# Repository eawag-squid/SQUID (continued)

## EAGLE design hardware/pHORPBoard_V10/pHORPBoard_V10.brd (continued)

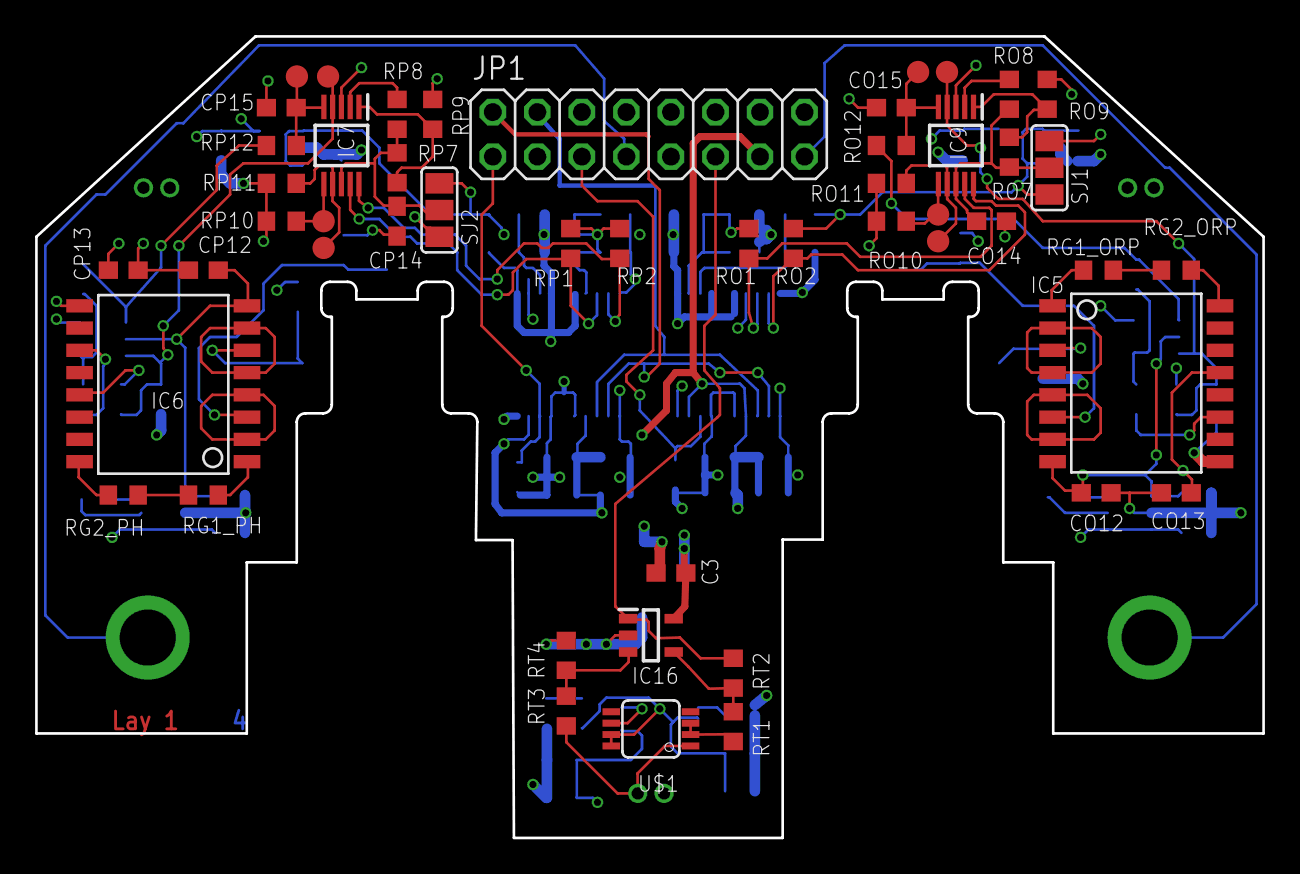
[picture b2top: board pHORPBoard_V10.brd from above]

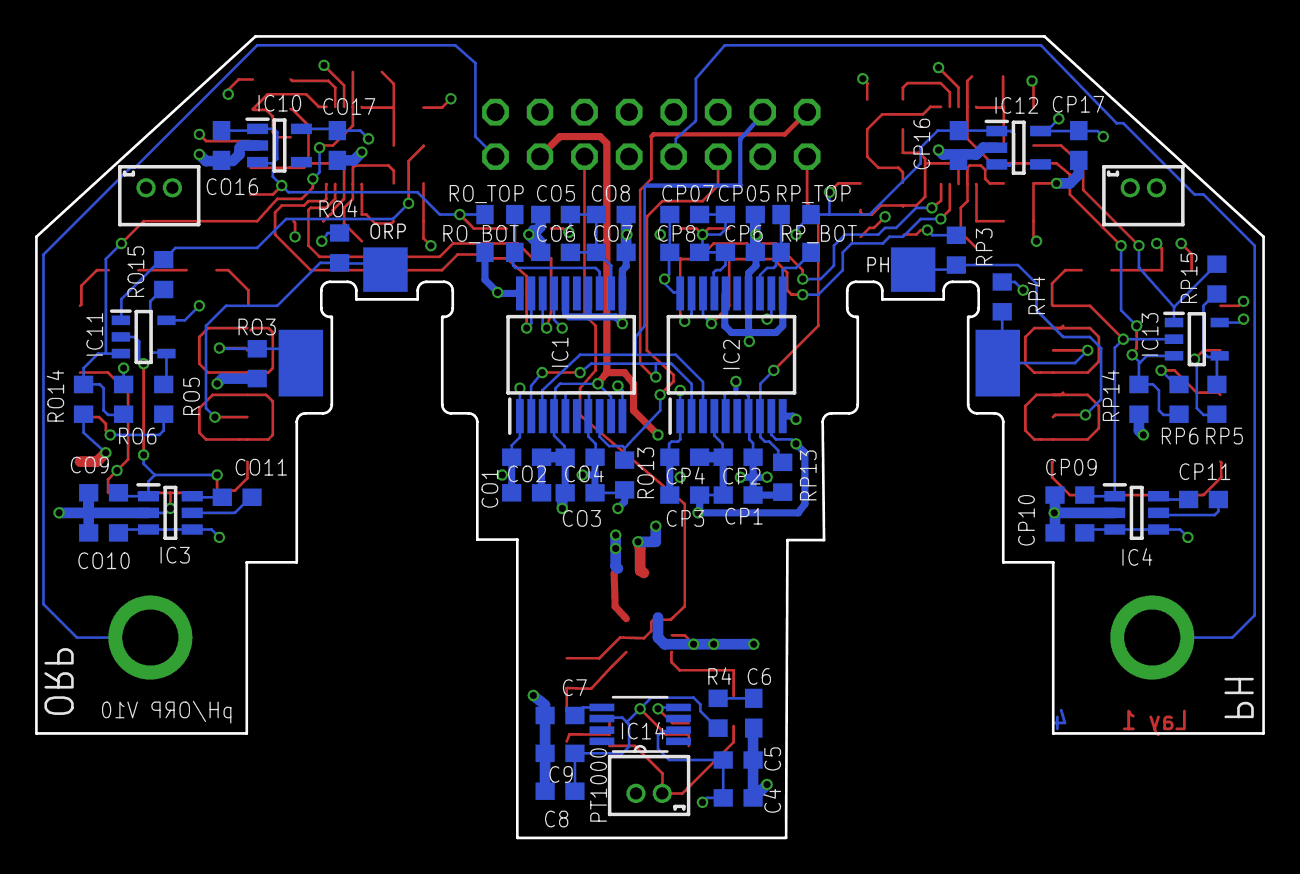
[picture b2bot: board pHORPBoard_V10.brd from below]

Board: 4 copper layers, 70.0 x 45.7 mm, 115 parts (65 on the bottom side), 67 nets.

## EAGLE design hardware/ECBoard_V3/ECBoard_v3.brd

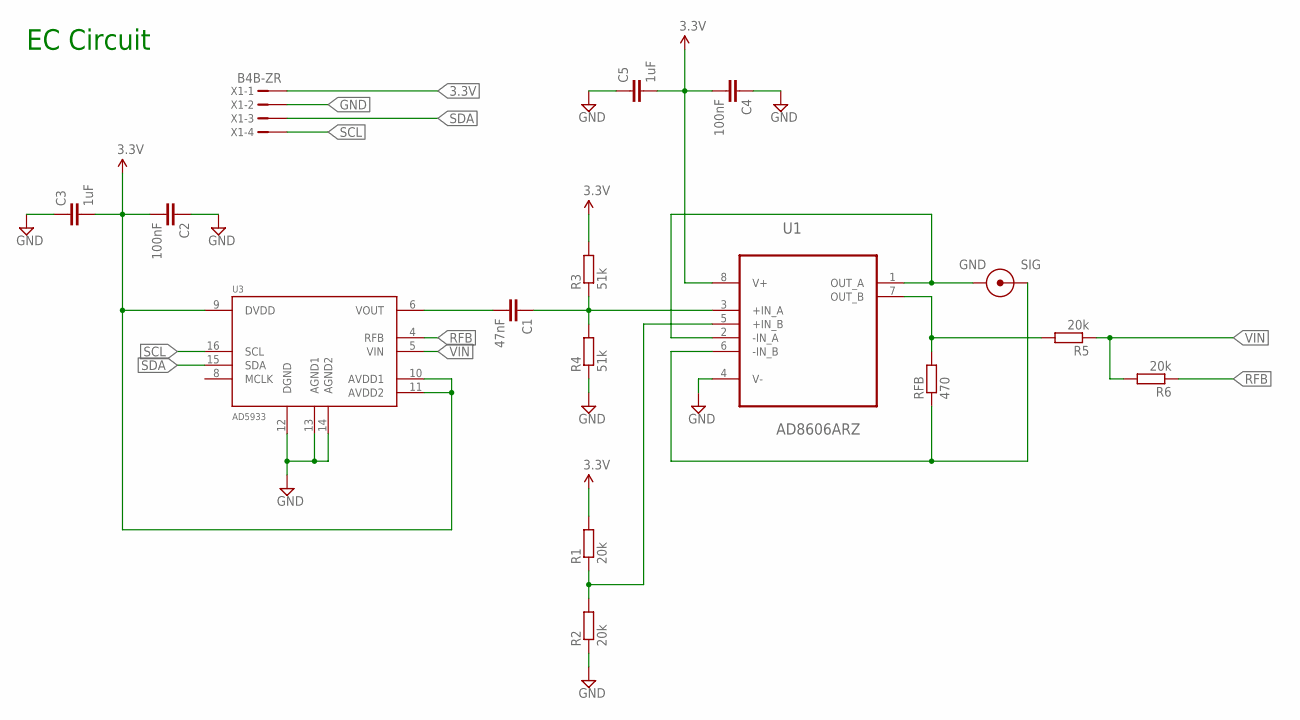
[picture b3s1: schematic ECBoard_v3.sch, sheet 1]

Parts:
C1: 47nF; C0805
C2, C4: 100nF; C0805
C3, C5: 1uF; C0805
R1, R2, R5, R6: 20k; R0805
R3, R4: 51k; R0805
RFB: 470; R0805
U1: AD8606ARZ; SOIC127P600X175-8N
U3: AD5933; SSOP16
U$1: CON_HANNA
X1: B4B-ZR

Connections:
3.3V: C2.2, C3.2, C4.2, C5.2, R1.2, R3.2, U1.8 (V+), U3.9 (DVDD), U3.10 (AVDD1), U3.11 (AVDD2), X1.1; also elsewhere on the board
GND: C2.1, C3.1, C4.1, C5.1, R2.1, R4.1, U1.4 (V-), U3.12 (DGND), U3.13 (AGND1), U3.14 (AGND2), X1.2; also elsewhere on the board
unnamed: C1.1, R3.1, R4.2, U1.3 (+IN_A)
unnamed: U1.1 (OUT_A), U1.2 (-IN_A), U$1.CON_GND
unnamed: C1.2, U3.6 (VOUT)
unnamed: RFB.1, U1.6 (-IN_B), U$1.CON_SIG
unnamed: R1.1, R2.2, U1.5 (+IN_B)
unnamed: R5.2, RFB.2, U1.7 (OUT_B)
RFB: R6.1, U3.4 (RFB)
SCL: U3.16 (SCL), X1.4
SDA: U3.15 (SDA), X1.3
VIN: R5.1, R6.2, U3.5 (VIN)

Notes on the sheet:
EC Circuit

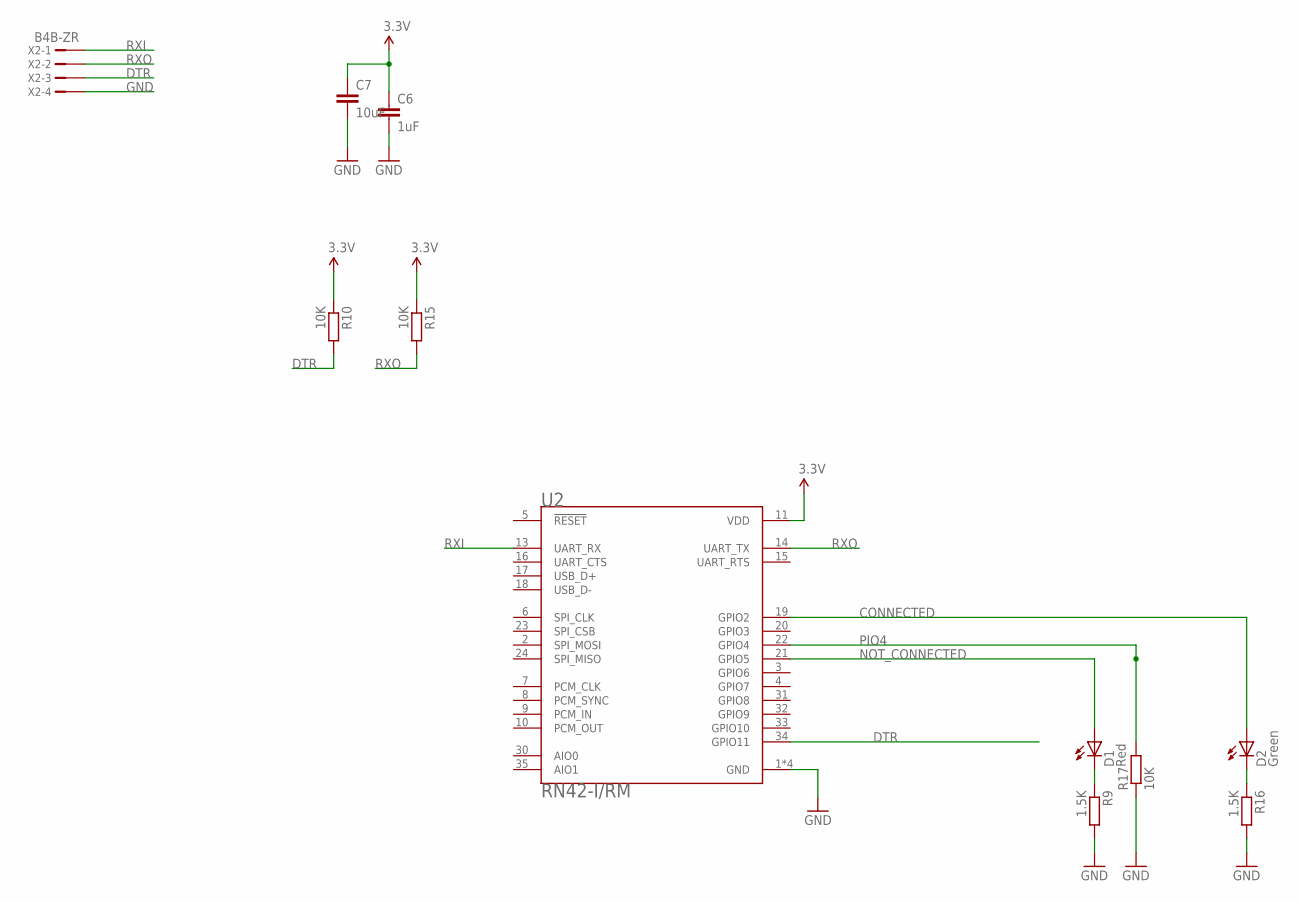
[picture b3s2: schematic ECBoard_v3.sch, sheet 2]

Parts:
C6: 1uF; C0805
C7: 10uF; C0805
D1: Red; LED-0603
D2: Green; LED-0603
R9, R16: 1.5K; R0805
R10, R15, R17: 10K; R0805
U2: RN42-I/RM; XCVR_RN42-I/RM
X2: B4B-ZR

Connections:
3.3V: C6.1, C7.1, R10.1, R15.1, U2.11 (VDD); also elsewhere on the board
CONNECTED: D2.A, U2.19 (GPIO2)
D1: D1.C, R9.1
D2: D2.C, R16.1
DTR: R10.2, U2.34 (GPIO11), X2.3
GND: C6.2, C7.2, R9.2, R16.2, R17.1, U2.1 (GND), U2.12 (GND), U2.28 (GND), U2.29 (GND), X2.4; also elsewhere on the board
NOT_CONNECTED: D1.A, U2.21 (GPIO5)
PIO4: R17.2, U2.22 (GPIO4)
RXI: U2.13 (UART_RX), X2.1
RXO: R15.2, U2.14 (UART_TX), X2.2

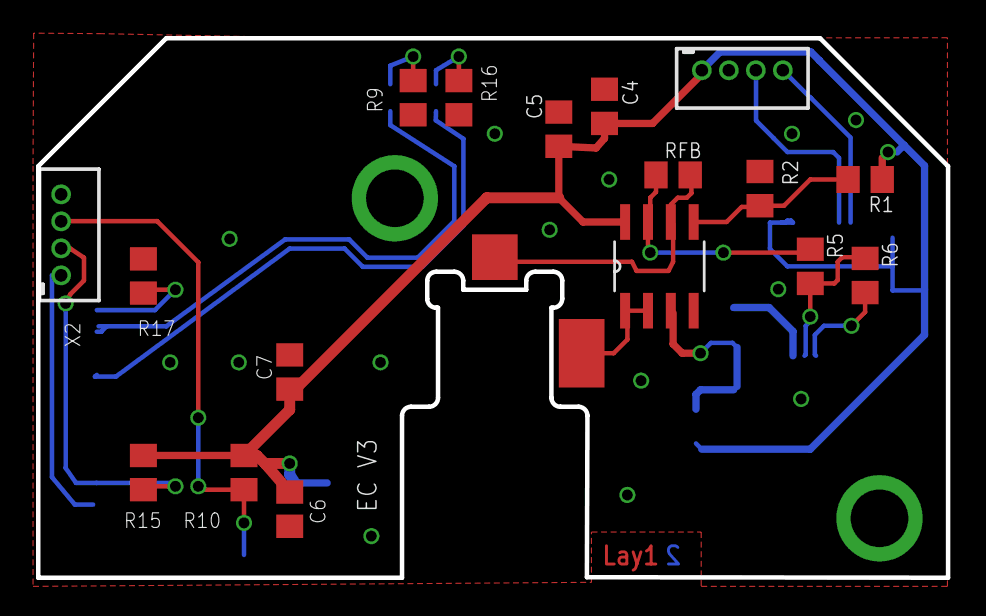
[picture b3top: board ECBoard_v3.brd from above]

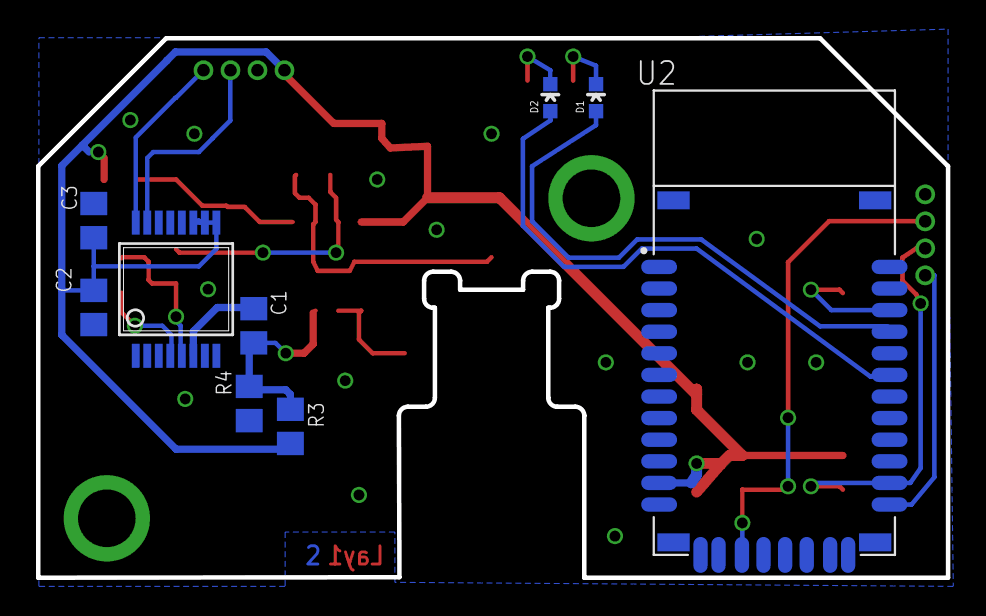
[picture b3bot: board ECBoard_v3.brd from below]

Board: 2 copper layers, 50.5 x 30.0 mm, 27 parts (9 on the bottom side), 20 nets.

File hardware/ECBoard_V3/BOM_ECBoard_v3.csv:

ECBoard_V3;;;;
;;;;
;;;;
;;;;
Reference designators;Quantity;MPN;Manufacturer;Description
R9, R16;2;GPR08051K5;Generic part;0805, Res 1.5kOhm, 150V, 1.0%, 125mW
C2, C4;2;GPC0805104;Generic part;0805, Cap 100.0nF, 50V, 10.0%, X7R
R10, R15, R17;3;GPR080510K;Generic part;0805, Res 10.0kOhm, 150V, 1.0%, 125mW
C7;1;GPC0805106-16;Generic part;0805 MLCC X5R 10UF 10% 16V
C3, C5, C6;3;GPC0805105;Generic part;0805, Cap 1uF, 50V, 10.0%, X7R
R1, R2, R5, R6;4;GPR080520K;Generic part;0805, Res 20.0kOhm, 150V, 1.0%, 125mW
RFB;1;GPR0805470R;Generic part;0805, Res 470.0Ohm, 150V, 1.0%, 125mW
C1;1;GPC0805473;Generic part;0805, Cap 47.0nF, 50V, 10.0%, X7R
R3, R4;2;GPR080551K;Generic part;0805, Res 51.0kOhm, 150V, 1.0%, 125mW
U3;1;AD5933YRSZ;Analog Device;Data Acquisition ADCs/DACs - Specialised IC 12bit 1 MSPS Impedance Cnvtr
U1;1;AD8606ARZ;Analog Devices;General Purpose Amplifier 2 Circuit Rail-to-Rail 8-SOIC
X1, X2;2;B4B-ZR(LF)(SN);JST;"4 Positions Header Connector 0.059"" (1.50mm) Through Hole Tin"
U4;1;RN42-I/RM;Microchip Technology;RF TXRX MOD BLUETOOTH TRACE ANT
D2;1;LT Q39E-Q1OO-25-1;OSRAM Opto Semiconductors Inc.;Green 530nm LED Indication - Discrete 2.85V 0603 (1608 Metric)
D1;1;LS Q976-NR-1;Osram Opto;Red 633nm LED Indication - Discrete 2V 0603 (1608 Metric)

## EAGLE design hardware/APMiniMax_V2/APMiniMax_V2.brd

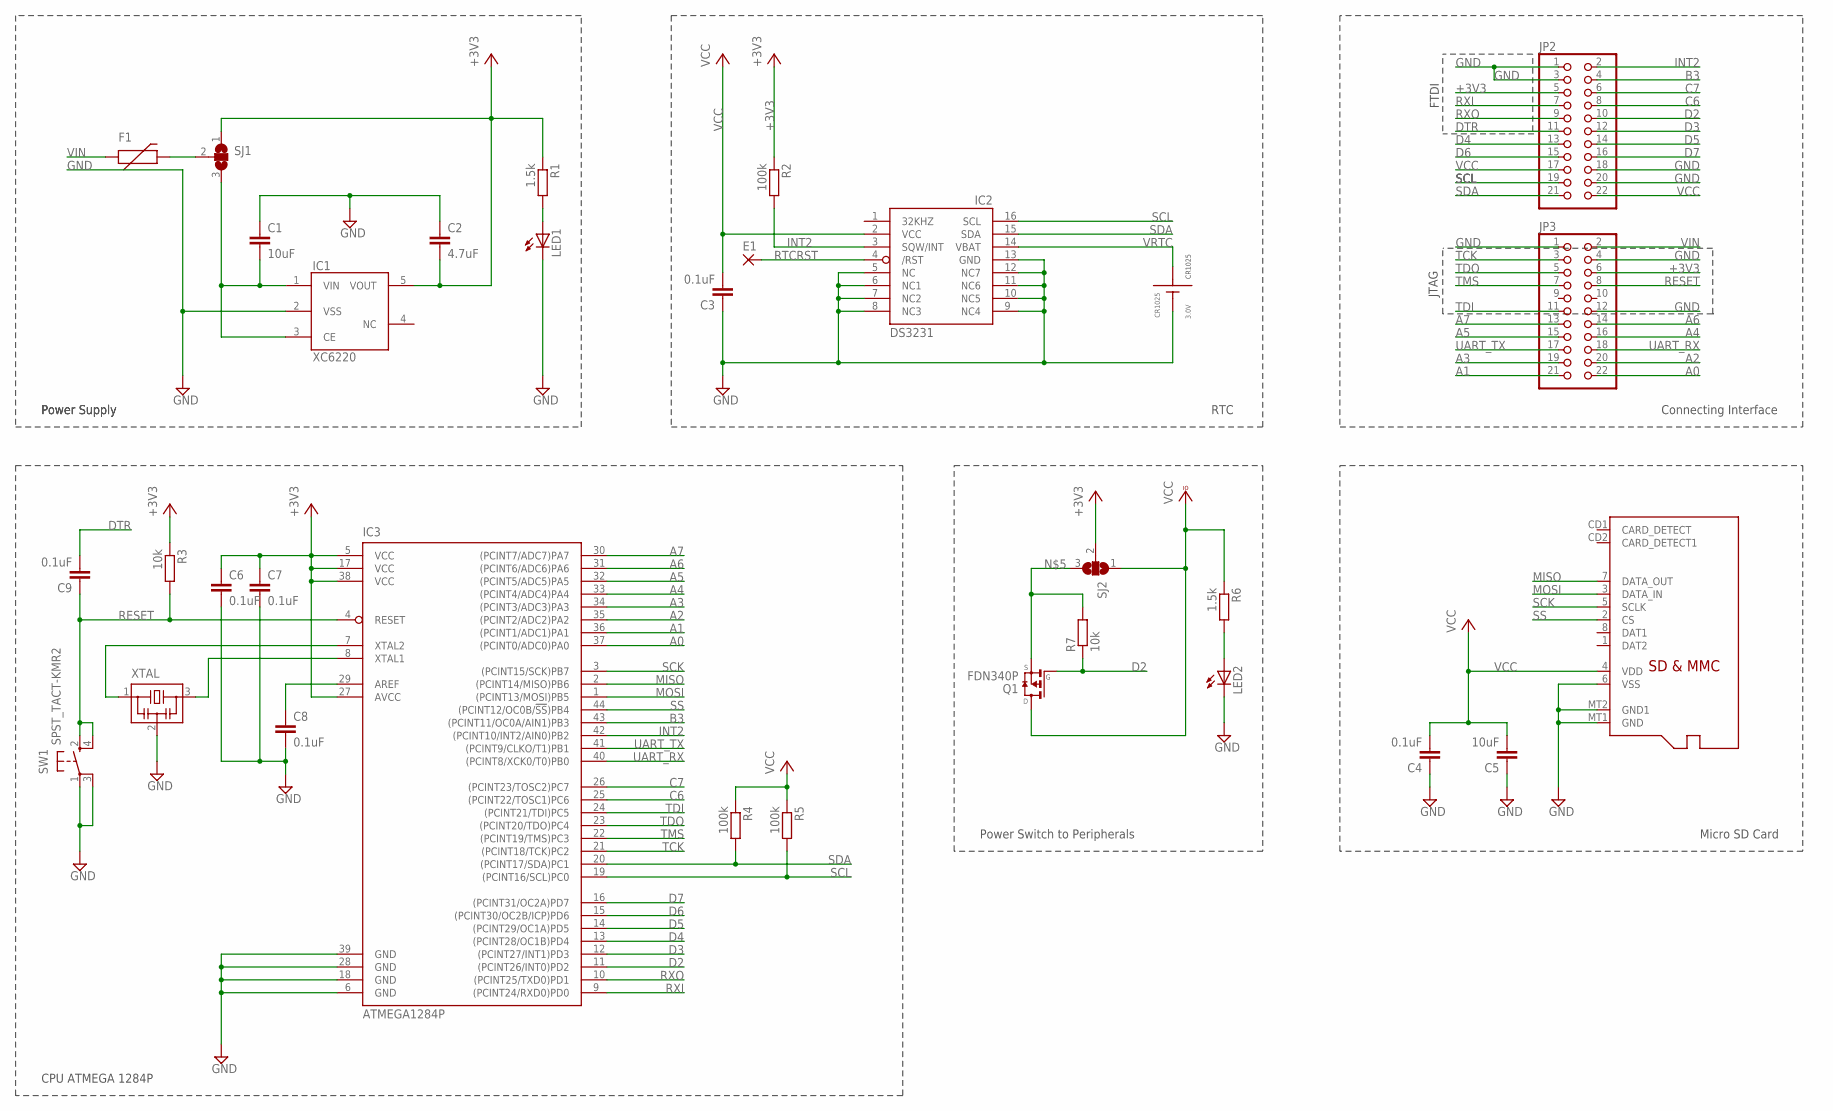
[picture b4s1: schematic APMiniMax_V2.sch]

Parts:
C1, C5: 10uF; C1206
C2: 4.7uF; C1206
C3, C4, C6, C7, C8, C9: 0.1uF; C0805
CR1025: 3.0V; CR1025SMD
E1: 0,75/0,5
F1: FUSE0805; R0805
IC1: XC6220SOT-25; SOT25
IC2: DS3231/SO; SO16W
IC3: ATMEGA1284P; TQFP44
JP2, JP3: PINHD-2X11; 2X11
LED1, LED2: LEDCHIP-LED0805; CHIP-LED0805
MMC: MICROSD
Q1: FDN340P; SSOT-3
R1, R6: 1.5k; R0805
R2, R4, R5: 100k; R0805
R3, R7: 10k; R0805
SJ1, SJ2: SJ2W; SJ_2
SW1: SPST_TACT-KMR2; KMR2
XTAL: CSTCE8M00G52-R0; CSTCE

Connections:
+3V3: C2.2, C6.1, C7.1, IC1.5 (VOUT), IC3.5 (VCC), IC3.17 (VCC), IC3.27 (AVCC), IC3.38 (VCC), JP2.5, JP3.6, R1.1, R2.1, R3.1, SJ1.1, SJ2.2
A0: IC3.37 ((PCINT0/ADC0)PA0), JP3.22
A1: IC3.36 ((PCINT1/ADC1)PA1), JP3.21
A2: IC3.35 ((PCINT2/ADC2)PA2), JP3.20
A3: IC3.34 ((PCINT3/ADC3)PA3), JP3.19
A4: IC3.33 ((PCINT4/ADC4)PA4), JP3.16
A5: IC3.32 ((PCINT5/ADC5)PA5), JP3.15
A6: IC3.31 ((PCINT6/ADC6)PA6), JP3.14
A7: IC3.30 ((PCINT7/ADC7)PA7), JP3.13
AREF: C8.1, IC3.29 (AREF)
B3: IC3.43 ((PCINT11/OC0A/AIN1)PB3), JP2.4
C6: IC3.25 ((PCINT22/TOSC1)PC6), JP2.8
C7: IC3.26 ((PCINT23/TOSC2)PC7), JP2.6
D2: IC3.11 ((PCINT26/INT0)PD2), JP2.10, Q1.1 (G), R7.1
D3: IC3.12 ((PCINT27/INT1)PD3), JP2.12
D4: IC3.13 ((PCINT28/OC1B)PD4), JP2.13
D5: IC3.14 ((PCINT29/OC1A)PD5), JP2.14
D6: IC3.15 ((PCINT30/OC2B/ICP)PD6), JP2.15
D7: IC3.16 ((PCINT31/OC2A)PD7), JP2.16
DTR: C9.2, JP2.11
GND: C1.1, C2.1, C3.1, C4.1, C5.1, C6.2, C7.2, C8.2, CR1025.GND, IC1.2 (VSS), IC2.5 (NC), IC2.6 (NC1), IC2.7 (NC2), IC2.8 (NC3), IC2.9 (NC4), IC2.10 (NC5), IC2.11 (NC6), IC2.12 (NC7), IC2.13 (GND), IC3.6 (GND), IC3.18 (GND), IC3.28 (GND), IC3.39 (GND), JP2.1, JP2.3, JP2.18, JP2.20, JP3.1, JP3.4, JP3.12, LED1.C, LED2.C, MMC.6 (VSS), MMC.MT1 (GND), MMC.MT2 (GND1), SW1.1, SW1.3 (P1), XTAL.2
INT2: IC2.3 (SQW/INT), IC3.42 ((PCINT10/INT2/AIN0)PB2), JP2.2, R2.2
MISO: IC3.2 ((PCINT14/MISO)PB6), MMC.7 (DATA_OUT)
MOSI: IC3.1 ((PCINT13/MOSI)PB5), MMC.3 (DATA_IN)
unnamed: LED1.A, R1.2
unnamed: F1.2, SJ1.2
unnamed: C1.2, IC1.1 (VIN), IC1.3 (CE), SJ1.3
unnamed: Q1.2 (S), R7.2, SJ2.3
unnamed: IC3.7 (XTAL2), XTAL.1
unnamed: IC3.8 (XTAL1), XTAL.3
unnamed: LED2.A, R6.2
RESET: C9.1, IC3.4 (RESET), JP3.8, R3.2, SW1.2 (S), SW1.4 (S1)
RTCRST: E1.1, IC2.4 (/RST)
RXI: IC3.9 ((PCINT24/RXD0)PD0), JP2.7
RXO: IC3.10 ((PCINT25/TXD0)PD1), JP2.9
SCK: IC3.3 ((PCINT15/SCK)PB7), MMC.5 (SCLK)
SCL: IC2.16 (SCL), IC3.19 ((PCINT16/SCL)PC0), JP2.19, R5.2
SDA: IC2.15 (SDA), IC3.20 ((PCINT17/SDA)PC1), JP2.21, R4.2
SS: IC3.44 ((PCINT12/OC0B/!SS!)PB4), MMC.2 (CS)
TCK: IC3.21 ((PCINT18/TCK)PC2), JP3.3
TDI: IC3.24 ((PCINT21/TDI)PC5), JP3.11
TDO: IC3.23 ((PCINT20/TDO)PC4), JP3.5
TMS: IC3.22 ((PCINT19/TMS)PC3), JP3.7
UART_RX: IC3.40 ((PCINT8/XCK0/T0)PB0), JP3.18
UART_TX: IC3.41 ((PCINT9/CLKO/T1)PB1), JP3.17
VCC: C3.2, C4.2, C5.2, IC2.2 (VCC), JP2.17, JP2.22, MMC.4 (VDD), Q1.3 (D), R4.1, R5.1, R6.1, SJ2.1
VIN: F1.1, JP3.2
VRTC: CR1025.V+@1 (V+), CR1025.V+@2 (V+), IC2.14 (VBAT)

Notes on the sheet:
JTAG
FTDI
Power Supply
CPU ATMEGA 1284P
RTC
Connecting Interface
Micro SD Card
Power Switch to Peripherals

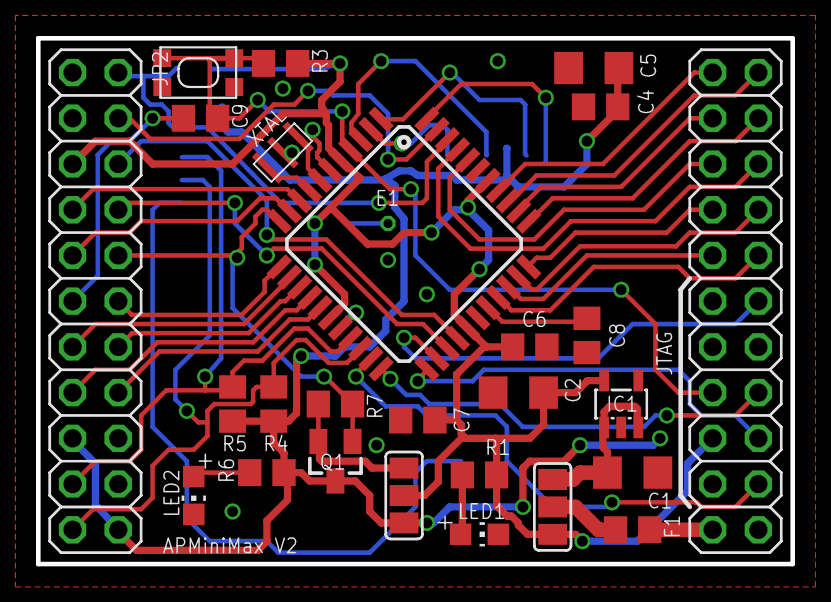
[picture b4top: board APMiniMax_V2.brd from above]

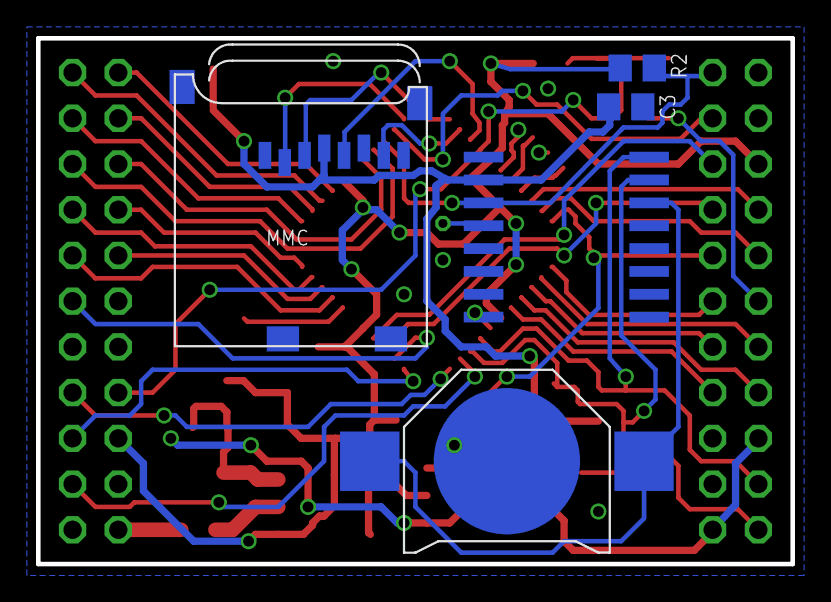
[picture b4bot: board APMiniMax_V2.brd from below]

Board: 2 copper layers, 41.9 x 29.2 mm, 32 parts (5 on the bottom side), 48 nets.

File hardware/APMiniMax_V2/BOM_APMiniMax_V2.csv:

APMiniMax;;;;
;;;;
Reference designators;Quantity;MPN;Manufacturer;Description
C1, C5;2;GPC1206106-B;Generic part;"10µF 25V Ceramic Capacitor X5R 1206 (3216 Metric) 0.126"" L x 0.063"" W (3.20mm x 1.60mm)"
C2;1;GPC1206475;Generic part;4.7µF ±10% 25V Ceramic Capacitor X7R 1206 (3216 Metric)
C3, C4, C6, C7, C8, C9;6;GPC0805104;Generic part;0805, Cap 100.0nF, 50V, 10.0%, X7R
F1;1;MF-PSMF035X-2;Bourns Inc.;Polymeric PTC Resettable Fuse 6V 350mA Ih Surface Mount 0805 (2012 Metric), Concave
IC1;1;XC6220B331MR-G;Torex Semiconductor;Linear Voltage Regulator IC Positive Fixed 1 Output 3.3V 1A SOT-25
IC2;1;DS3231SN#;Maxim Integrated;IC, Extremely Accurate I2C-Integrated RTC/TCXO/Crystal
IC3;1;ATMEGA1284P-AU;Atmel;ATmega Microcontroller IC 8-Bit 20MHz 128KB (64K x 16) FLASH 44-TQFP (10x10)
LED1, LED2;2;LTST-C171GKT;Lite-On;Green 569nm LED Indication - Discrete 2.1V 0805 (2012 Metric)
MMC;1;2908-05WB-MG;3M;10 (8 + 2) Position Card Connector Secure Digital - microSDâ¢ Surface Mount, Right Angle Gold
Q1;1;FDN340P;Fairchild Semiconductor;MOSFETP-Channel 20V 2A (Ta) 500mW (Ta) Surface Mount SuperSOT-3
R1, R6;2;GPR08051K5;Generic part;0805, Res 1.5kOhm, 150V, 1.0%, 125mW
R2, R4, R5;3;GPR0805100K;Generic part;0805, Res 100.0kOhm, 150V, 1.0%, 125mW
R3, R7;2;GPR080510K;Generic part;0805, Res 10.0kOhm, 150V, 1.0%, 125mW
SW1;1;KMR231NG LFS;C&K;Tactile Switch SPST-NO Top Actuated Surface Mount
XTAL;1;CSTCE8M00G52Z-R0;Murata;8MHz Ceramic Resonator Built in Capacitor 10pF ±0.1% -40°C ~ 125°C Surface Mount
CR1025;1;BK-870;MPD;Battery Retainer Coin, 10.0mm 1 Cell SMD (SMT) Tab

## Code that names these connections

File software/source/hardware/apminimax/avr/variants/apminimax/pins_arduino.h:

#ifndef Pins_Arduino_h
#define Pins_Arduino_h

#include <avr/pgmspace.h>

//                    ATMEL ATMEGA1284P 
//                    Pinout with VQFN case, just for visualization
//
//                               +---\/---+
//            PCINT8 (D14) PB0  1|        |40  PA0 (AI 0 / D24) PCINT0
//            PCINT9 (D15) PB1  2|        |39  PA1 (AI 1 / D25) PCINT1
//      PCINT10/INT2 (D 8) PB2  3|        |38  PA2 (AI 2 / D26) PCINT2
//      PCINT11/OC0A*(D 9) PB3  4|        |37  PA3 (AI 3 / D27) PCINT3
//   PCINT12/0C0B/SS*(D10) PB4  5|        |36  PA4 (AI 4 / D28) PCINT4
//      PCINT13/MOSI (D11) PB5  6|        |35  PA5 (AI 5 / D29) PCINT5
// PCINT14/OC3A/MISO*(D12) PB6  7|        |34  PA6 (AI 6 / D30) PCINT6
//  PCINT15/OC3B/SCK*(D13) PB7  8|        |33  PA7 (AI 7 / D31) PCINT7
//                         RST  9|        |32  AREF
//                         VCC 10|        |31  GND
//                         GND 11|        |30  AVCC
//                       XTAL2 12|        |29  PC7 (D23) TOSC2/PCINT23
//                       XTAL1 13|        |28  PC6 (D22) TOSC1/PCINT22
//       PCINT24/RX0 (D 0) PD0 14|        |27  PC5 (D21) TDI/PCINT21
//       PCINT25/TX0 (D 1) PD1 15|        |26  PC4 (D20) TDO/PCINT20
//  PCINT26/INT0/RX1 (D 2) PD2 16|        |25  PC3 (D19) TMS/PCINT19
//  PCINT27/INT1/TX1 (D 3) PD3 17|        |24  PC2 (D18) TCK/PCINT18
//      PCINT28/OC1B*(D 4) PD4 18|        |23  PC1 (D17) SDA/PCINT17
//      PCINT29/OC1A*(D 5) PD5 19|        |22  PC0 (D16) SCL/PCINT16
//      PCINT30/OC2B*(D 6) PD6 20|        |21  PD7 (D 7)*OC2A/PCINT31
//                               +--------+
// * = PWM capable pin
// TOSCn = RTC Crystal pinout
// TCK/TMS/TDO/TDI = JTAG pinout//

/* orig
   PCINT15-8: D7-0  : bit 1
   PCINT31-24: D15-8  : bit 3
   PCINT23-16: D23-16 : bit 2
   PCINT7-0: D31-24   : bit 0
   */

/* new
                         PCICR
   PCINT7-0:   D31-24  : bit 0
   PCINT15-8:  D15- 8  : bit 1
   PCINT23-16: D23-16  : bit 2
   PCINT31-24: D 7- 0  : bit 3
*/

#define NUM_DIGITAL_PINS            (32)
#define NUM_ANALOG_INPUTS           (8)

#define PIN_SPI_SS    (10)
#define PIN_SPI_MOSI  (11)
#define PIN_SPI_MISO  (12)
#define PIN_SPI_SCK   (13)

static const uint8_t SS   = PIN_SPI_SS;
static const uint8_t MOSI = PIN_SPI_MOSI;
static const uint8_t MISO = PIN_SPI_MISO;
static const uint8_t SCK  = PIN_SPI_SCK;

#define PIN_WIRE_SDA  (17)
#define PIN_WIRE_SCL  (16)

static const uint8_t SDA = PIN_WIRE_SDA;
static const uint8_t SCL = PIN_WIRE_SCL;


static const uint8_t A0 = 24;
static const uint8_t A1 = 25;
static const uint8_t A2 = 26;
static const uint8_t A3 = 27;
static const uint8_t A4 = 28;
static const uint8_t A5 = 29;
static const uint8_t A6 = 30;
static const uint8_t A7 = 31;

static const uint8_t PIN_RTC_INT = 8;

static const uint8_t PIN_UART1_RX = 14;
static const uint8_t PIN_UART1_TX = 15;

static const uint8_t PIN_VCCIO_ON = 2;

static const uint8_t PIN_C6 = 22;
static const uint8_t PIN_C7 = 23;
static const uint8_t PIN_B3 = 9;


//----------------------------------

#define analogInputToDigitalPin(p) ( ((p) < NUM_ANALOG_INPUTS) ? ((p) + 24) : -1)

#define analogPinToChannel(p)   ( ((p) >= 0 && (p) <= 7) ? ((p) + 24) : -1 )

#define digitalPinHasPWM(p)     ((p) == 4 || (p) == 5 || (p) == 6 || (p) == 7 || (p) == 9 || (p) == 10 || (p) == 12 || (p) == 13)

#define digitalPinToPCICR(p)    (((p) >= 0 && (p) < NUM_DIGITAL_PINS) ? (&PCICR) : ((uint8_t *)0))
#define digitalPinToPCICRbit(p) (((p) <= 7) ? 3 : (((p) <= 15) ? 1 : (((p) <= 23) ? 2 : 0)))
#define digitalPinToPCMSK(p)    (((p) <= 7) ? (&PCMSK3) : (((p) <= 15) ? (&PCMSK1) : (((p) <= 23) ? (&PCMSK2) : (&PCMSK0) )))
// The special case here, created by keeping the SPI interface on Arduino Uno pin numbering.
#define digitalPinToPCMSKbit(p) (((p) > 7 && (p) < 16) ? (((p) < 14 ? (p)+2 : (p)-6) % 8) : ((p) % 8)) 


#define digitalPinToInterrupt(p)  ((p) == 2 ? 0 : ((p) == 3 ? 1 : ((p) == 8 ? 2 : NOT_AN_INTERRUPT)))


#ifdef ARDUINO_MAIN

#define PA 1
#define PB 2
#define PC 3
#define PD 4

// these arrays map port names (e.g. port B) to the
// appropriate addresses for various functions (e.g. reading
// and writing)
const uint16_t PROGMEM port_to_mode_PGM[] =
{
	NOT_A_PORT,
	(uint16_t) &DDRA,
	(uint16_t) &DDRB,
	(uint16_t) &DDRC,
	(uint16_t) &DDRD,
};

const uint16_t PROGMEM port_to_output_PGM[] =
{
	NOT_A_PORT,
	(uint16_t) &PORTA,
	(uint16_t) &PORTB,
	(uint16_t) &PORTC,
	(uint16_t) &PORTD,
};

const uint16_t PROGMEM port_to_input_PGM[] =
{
	NOT_A_PORT,
	(uint16_t) &PINA,
	(uint16_t) &PINB,
	(uint16_t) &PINC,
	(uint16_t) &PIND,
};


const uint8_t PROGMEM digital_pin_to_port_PGM[] =
{
	PD, /* 0 */
	PD,
	PD,
	PD,
	PD,
	PD,
	PD,
	PD,
	PB, /* 8 */
	PB,
	PB,
	PB,
	PB,
	PB,
	PB,
	PB,
	PC, /* 16 */
	PC,
	PC,
	PC,
	PC,
	PC,
   	PC,
	PC,
	PA, /* 24 */
	PA,
	PA,
	PA,
	PA,
	PA,
	PA,
	PA  /* 31 */
};

const uint8_t PROGMEM digital_pin_to_bit_mask_PGM[] =
{
	_BV(0), /* 0, port D */
	_BV(1),
	_BV(2),
	_BV(3),
	_BV(4),
	_BV(5),
	_BV(6),
	_BV(7),
	_BV(2), /* 8, port B */
	_BV(3),
	_BV(4),
	_BV(5),
	_BV(6),
	_BV(7),
	_BV(0),
	_BV(1),
	_BV(0), /* 16, port C */
	_BV(1),
	_BV(2),
	_BV(3),
	_BV(4),
	_BV(5),
	_BV(6),
	_BV(7),
	_BV(0), /* 24, port A */
	_BV(1),
	_BV(2),
	_BV(3),
	_BV(4),
	_BV(5),
	_BV(6),
	_BV(7)
};

const uint8_t PROGMEM digital_pin_to_timer_PGM[] =
{
	NOT_ON_TIMER, 	/* 0  - PD0 */
	NOT_ON_TIMER, 	/* 1  - PD1 */
	NOT_ON_TIMER, 	/* 2  - PD2 */
	NOT_ON_TIMER, 	/* 3  - PD3 */
	TIMER1B,     	/* 4  - PD4 */
	TIMER1A,     	/* 5  - PD5 */
	TIMER2B,     	/* 6  - PD6 */
	TIMER2A,     	/* 7  - PD7 */

	NOT_ON_TIMER, 	/* 8  - PB2 */
	TIMER0A,     	/* 9  - PB3 */
	TIMER0B,        /* 10 - PB4 */
	NOT_ON_TIMER, 	/* 11 - PB5 */
	TIMER3A,        /* 12 - PB6 */
	TIMER3B,        /* 13 - PB7 */

	NOT_ON_TIMER, 	/* 14 - PB0 */
	NOT_ON_TIMER, 	/* 15 - PB1 */

	NOT_ON_TIMER, 	/* 16 - PC0 */
	NOT_ON_TIMER,   /* 17 - PC1 */
	NOT_ON_TIMER,   /* 18 - PC2 */
	NOT_ON_TIMER,   /* 19 - PC3 */
	NOT_ON_TIMER,   /* 20 - PC4 */
	NOT_ON_TIMER,   /* 21 - PC5 */
	NOT_ON_TIMER,   /* 22 - PC6 */
	NOT_ON_TIMER,   /* 23 - PC7 */
	
	NOT_ON_TIMER,   /* 24 - PA0 */
	NOT_ON_TIMER,   /* 25 - PA1 */
	NOT_ON_TIMER,   /* 26 - PA2 */
	NOT_ON_TIMER,   /* 27 - PA3 */
	NOT_ON_TIMER,   /* 28 - PA4 */
	NOT_ON_TIMER,   /* 29 - PA5 */
	NOT_ON_TIMER,   /* 30 - PA6 */
	NOT_ON_TIMER    /* 31 - PA7 */
};

#endif // ARDUINO_MAIN

// These serial port names are intended to allow libraries and architecture-neutral
// sketches to automatically default to the correct port name for a particular type
// of use.  For example, a GPS module would normally connect to SERIAL_PORT_HARDWARE_OPEN,
// the first hardware serial port whose RX/TX pins are not dedicated to another use.
//
// SERIAL_PORT_MONITOR        Port which normally prints to the Arduino Serial Monitor
//
// SERIAL_PORT_USBVIRTUAL     Port which is USB virtual serial
//
// SERIAL_PORT_LINUXBRIDGE    Port which connects to a Linux system via Bridge library
//
// SERIAL_PORT_HARDWARE       Hardware serial port, physical RX & TX pins.
//
// SERIAL_PORT_HARDWARE_OPEN  Hardware serial ports which are open for use.  Their RX & TX
//                            pins are NOT connected to anything by default.
#define SERIAL_PORT_MONITOR         Serial
#define SERIAL_PORT_HARDWARE        Serial
#define SERIAL_PORT_HARDWARE1       Serial1
#define SERIAL_PORT_HARDWARE_OPEN   Serial1


#endif // Pins_Arduino_h
// vim:ai:cin:sts=2 sw=2 ft=cpp

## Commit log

2018-01-13 Create files
2019-04-15 Add files via upload
    -> images for EC Wiki entry
2019-04-17 Created a new folder for the SQUID_zGUI installers
2019-04-17 moving installers for SQUID_zGUI to separate repository
2019-04-17 Current format for firmware version V4 and newer
2019-04-17 new configuration file for firmware version V5
2019-04-17 configuration files moved to separate folder
2019-04-17 version V5.1
    Compatibility:
    - this firmware can only be used for hardware built later than December 2018 with the new pHORPBoard V7 and newer
    New features and modifications
    - new calibration method: 3 point calibration for pH, single point calibration for EC
    - fixed bug: store EC values with more digits on MIcroSD card, time and data for files on MicroSD card
    - support for Bluetooth modem
2019-04-18 Menu text modified
2019-05-08 user menu for calibration optimized
2019-09-24 improved timing and new system configuration menu
2019-09-24 added new parameters
    parameters for measurement cycle and energy consumtion (buzzer/LED control) added
2019-11-29 - current version with bluetooth and magnetic switch
2020-01-20 - hardware support for software shutdown (modified CarrierBoard V6 and newer)
2020-01-20 - V5.3 hardware support for software shutdown (modified CarrierBoard V6 and newer)
2020-01-20 - folder renamed
2020-01-20 - update V5.3
2021-02-11 - fixed config issue with alpha value - fixed hanging EC reading - writing serial number does not require separate firmware
2021-02-11 - new config file for firmware V5.5
2021-02-11 . new version V5.5
2021-02-11 - new version V5.5
